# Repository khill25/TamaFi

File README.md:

<div align="center">

  <h1> TamaFi </h1>
  <p> TamaFi is an open-source, WiFi-enabled virtual pet </p>

<!-- Badges -->

<h4>
    <a href="https://twitter.com/techcifer">TWITTER</a>
  <span> · </span>
    <a href="https://www.instagram.com/cifertech/">INSTAGRAM</a>
  <span> · </span>
    <a href="https://www.youtube.com/@techcifer">YOUTUBE</a>
  <span> · </span>
    <a href="https://cifertech.net/">WEBSITE</a>
  </h4>
</div>

<br />

<div>&nbsp;</div>

## 📖 Explore the Full Documentation

Ready to dive deeper into TamaFi's details? Discover the full story, in-depth tutorials, and all the exciting features in our comprehensive [documentation](https://cifertech.net/tamafi-reviving-the-classic-virtual-pet-with-a-tech-twist/). Click the link and explore further!
  
<div>&nbsp;</div>

<!-- About the Project -->
## :star2: About the Project
TamaFi is a modern reimagining of the classic Tamagotchi, aiming to blend nostalgia with modern technology. Built with an ESP32 microcontroller and a vibrant TFT LCD, TamaFi offers a unique twist: feeding your virtual pet through Wi-Fi scanning.

Why TamaFi?
- Classic Tamagotchis lacked vibrant graphics, backlighting, and modern interactions.
- TamaFi fills this gap by offering an enhanced virtual pet experience with open-source versatility.

<div align="center"> 
  
</div>

<div>&nbsp;</div>

<h2>🛠 Functionality Status and Reliability</h2>

TamaFi is a work-in-progress and has room for improvement. While it’s functional and exciting to use, there’s always room to make it better, more reliable, and feature-rich. Whether it’s optimizing the code, enhancing the design, or suggesting new features, your contributions are highly welcomed!

<table>
  <thead>
    <tr>
      <th>Feature</th>
      <th>Status</th>
      <th>Details</th>
    </tr>
  </thead>
  <tbody>
    <tr>
      <td>Pet Animation</td>
      <td>⚠ Stable</td>
      <td>Includes hatching, random, and stat-based animations.</td>
    </tr>
    <tr>
      <td>Stat Management</td>
      <td>⚠ Stable</td>
      <td>Hunger, happiness, and hygiene stats are tracked and updated.</td>
    </tr>
    <tr>
      <td>Wi-Fi Feeding</td>
      <td>🚧 In Progress</td>
      <td>Detects nearby networks and feeds the pet.</td>
    </tr>
    <tr>
      <td>TFT LCD Display</td>
      <td>✅ Reliable</td>
      <td>Displays sprites, stats, and animations with smooth transitions.</td>
    </tr>
    <tr>
      <td>Button Inputs</td>
      <td>⚠ Stable</td>
      <td>Three microswitches handle user interaction.</td>
    </tr>
    <tr>
      <td>PCB Design</td>
      <td>✅ Verified</td>
      <td>Tested for compatibility and efficient layout.</td>
    </tr>
    <tr>
      <td>RGB LED and Buzzer Integration</td>
      <td>🚧 In Progress</td>
      <td>Planned for the next release.</td>
    </tr>
  </tbody>
</table>

<div>&nbsp;</div>

<!-- Features -->
### 🎯 Features

**Hardware:**

- ESP32-U4 microcontroller
- TFT LCD (ST7789) with vibrant visuals
- WS2812 RGB LED for colorful effects
- Buzzer for sound alerts
- TP4056 charging module with USB-C
- LF33 voltage regulator

**Software:**

- Custom animations for pets and stats
- WiFi-based feeding system
- Interactive buttons for actions
- Egg-hatching and pet-death animations
- Open-source and easily customizable

<div>&nbsp;</div>

<!-- License -->
## :warning: License

Distributed under the MIT License. See LICENSE.txt for more information.

<div>&nbsp;</div>

<!-- Contact -->
## :handshake: Contact

▶ Support me on Patreon [patreon.com/cifertech](https://www.patreon.com/cifertech)

CiferTech - [@twitter](https://twitter.com/techcifer) - CiferTech@gmali.com

Project Link: [https://github.com/cifertech/TamaFi](https://github.com/cifertech/TamaFi)

<div>&nbsp;</div>

<!-- Acknowledgments -->
## :gem: Acknowledgements 

**The libraries and projects listed below are used in this software:**
 - [Mecha-Stone Golem](https://darkpixel-kronovi.itch.io/mecha-golem-free)
 - [Fantasy Wooden GUI](https://kanekizlf.itch.io/fantasy-wooden-gui-free)
 - [MyPixelWorld](https://scarloxy.itch.io/mpwsp01)
 - [Transparent Sprites](https://github.com/VolosR/SpritesTuT)

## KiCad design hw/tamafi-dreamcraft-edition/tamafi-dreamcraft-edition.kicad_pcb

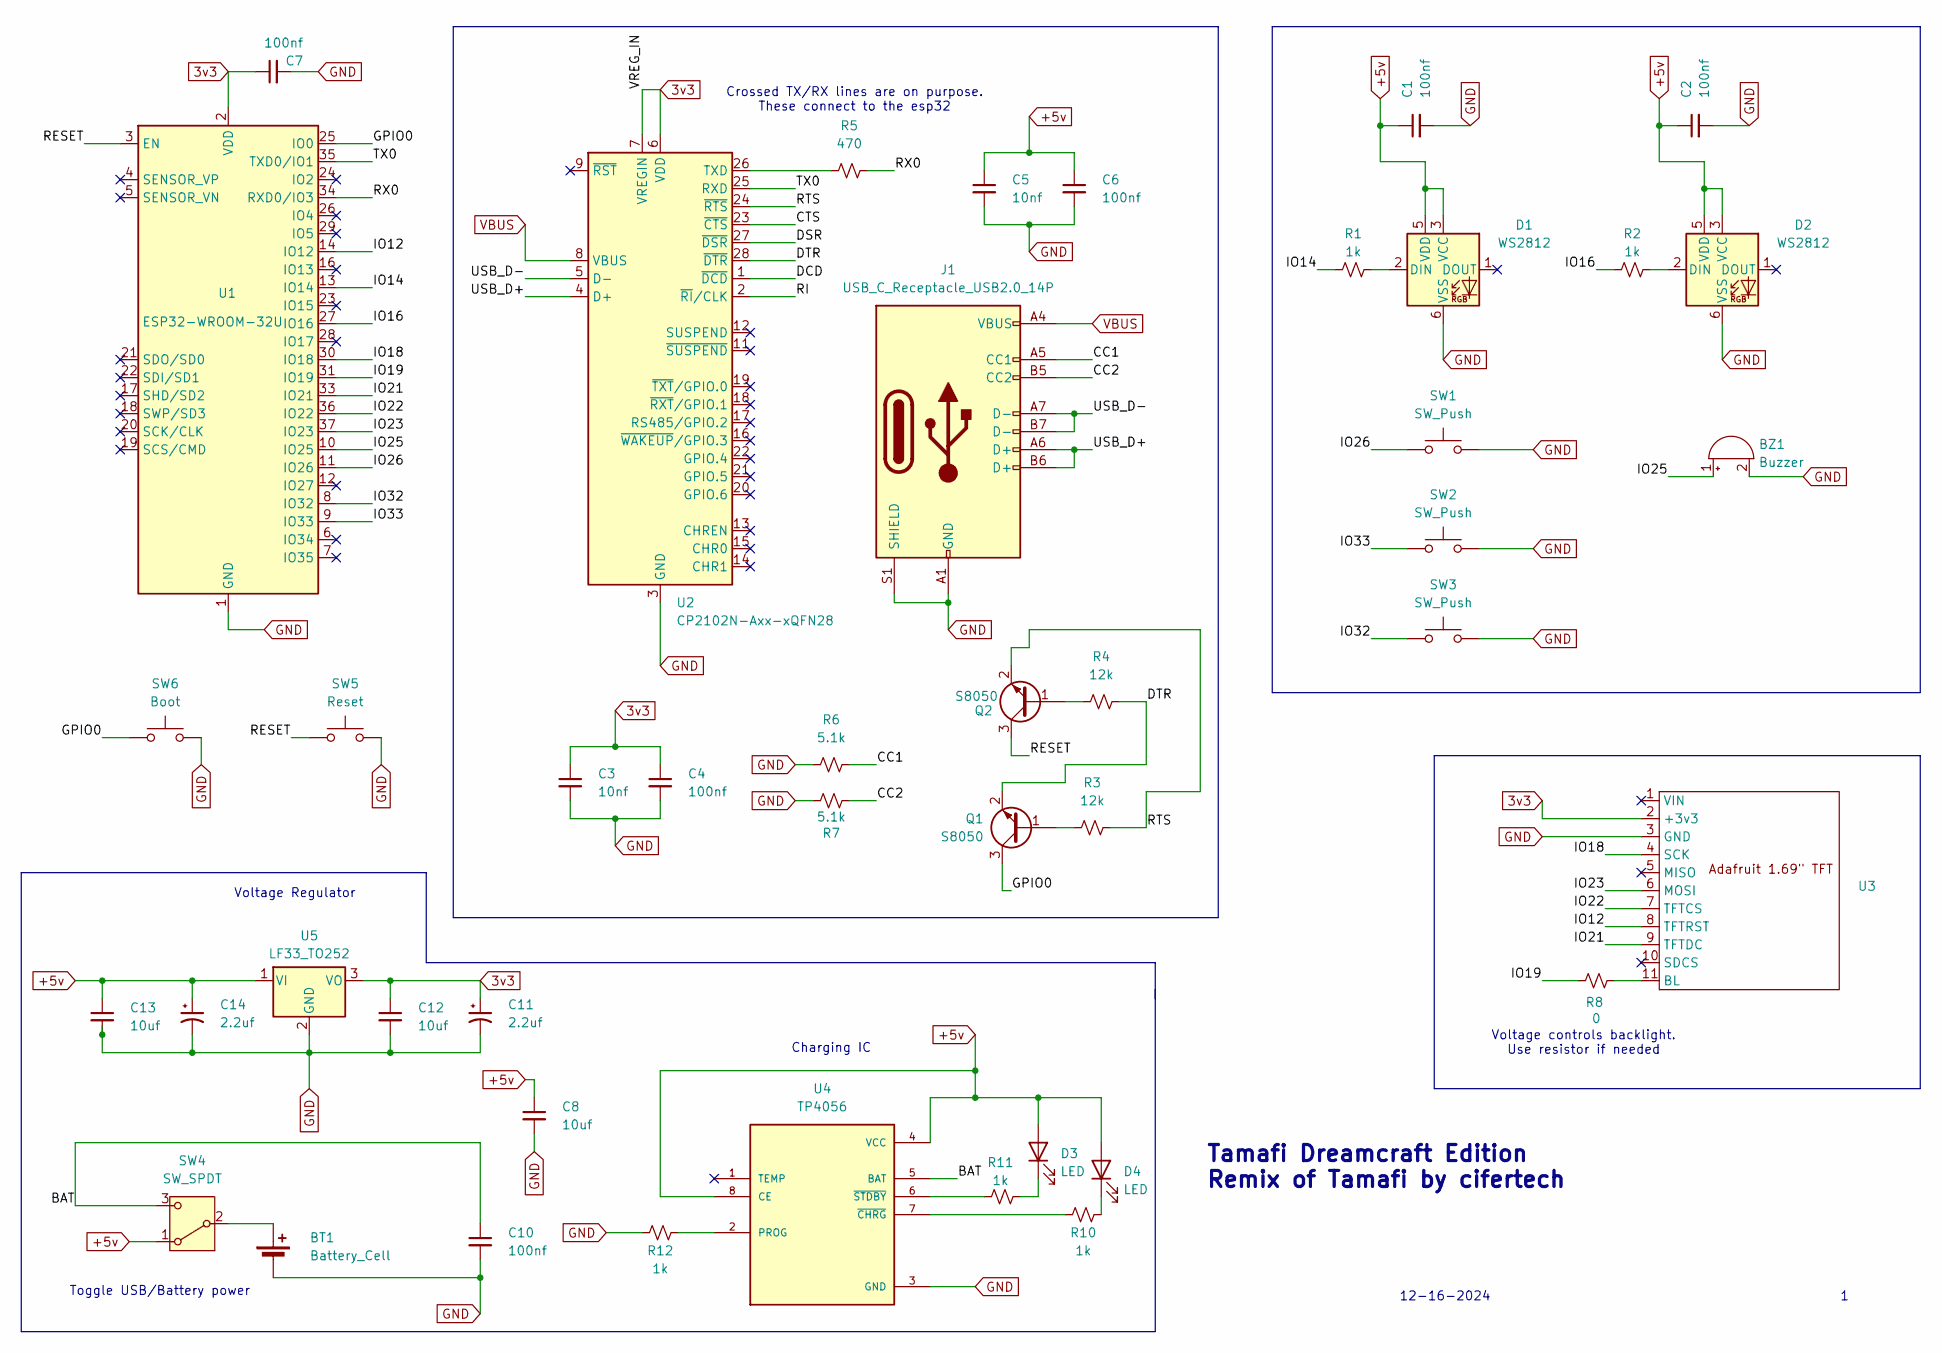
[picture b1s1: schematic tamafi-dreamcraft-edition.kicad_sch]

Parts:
BT1: Battery_Cell; JST_PH_B2B-PH-K_1x02_P2.00mm_Vertical
BZ1: Buzzer; Buzzer_12x9.5RM7.6
C1, C2, C4, C6, C7, C10: 100nf; C_0805_2012Metric
C3, C5: 10nf; C_0805_2012Metric
C8, C12, C13: 10uf; C_0805_2012Metric
C11, C14: 2.2uf; C_0805_2012Metric
D1, D2: WS2812; LED_WS2812_PLCC6_5.0x5.0mm_P1.6mm
D3, D4: LED; LED_0805_2012Metric_Pad1.15x1.40mm_HandSolder
J1: USB_C_Receptacle_USB2.0_14P; USB_C_Receptacle_HRO_TYPE-C-31-M-12
Q1, Q2: S8050; SOT-23
R1, R2, R10, R11, R12: 1k; R_0805_2012Metric
R3, R4: 12k; R_0805_2012Metric
R5: 470; R_0805_2012Metric
R6, R7: 5.1k; R_0805_2012Metric
R8: 0; R_0805_2012Metric
SW1, SW2, SW3: SW_Push; SW_SPST_B3S-1000
SW4: SW_SPDT; SW_Slide-03_Wuerth-WS-SLTV_10x2.5x6.4_P2.54mm
SW5: Reset; SW_SPST_FSMSM
SW6: Boot; SW_SPST_FSMSM
U1: ESP32-WROOM-32U
U2: CP2102N-Axx-xQFN28; QFN-28-1EP_5x5mm_P0.5mm_EP3.35x3.35mm
U3: Adafruit 1.69in 280x240 TFT
U4: TP4056; SOP-8_3.9x4.9mm_P1.27mm
U5: LF33_TO252; TO-252-2

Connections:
3v3: C3.1, C4.1, C7.1, C11.1, C12.1, U1.2 (VDD), U2.6 (VDD), U2.7 (VREGIN), U3.2 (+3v3), U5.3 (VO)
+5v: C1.1, C2.1, C5.1, C6.1, C8.1, C13.1, C14.1, D1.3 (VCC), D1.5 (VDD), D2.3 (VCC), D2.5 (VDD), D3.2 (A), D4.2 (A), SW4.1 (A), U4.4 (VCC), U4.8 (CE), U5.1 (VI)
/BAT: C10.1, SW4.3 (C), U4.5 (BAT)
/CC1: J1.A5 (CC1), R6.2
/CC2: J1.B5 (CC2), R7.2
/CTS: U2.23 (~CTS)
/DCD: U2.1 (~DCD)
/DSR: U2.27 (~DSR)
/DTR: Q1.2 (E), R4.2, U2.28 (~DTR)
/GPIO0: Q1.3 (C), SW6.1, U1.25 (IO0)
/IO12: U1.14 (IO12), U3.8 (TFTRST)
/IO14: R1.2, U1.13 (IO14)
/IO16: R2.2, U1.27 (IO16)
/IO18: U1.30 (IO18), U3.4 (SCK)
/IO19: R8.2, U1.31 (IO19)
/IO21: U1.33 (IO21), U3.9 (TFTDC)
/IO22: U1.36 (IO22), U3.7 (TFTCS)
/IO23: U1.37 (IO23), U3.6 (MOSI)
/IO25: BZ1.1 (+), U1.10 (IO25)
/IO26: SW1.1, U1.11 (IO26)
/IO32: SW3.1, U1.8 (IO32)
/IO33: SW2.1, U1.9 (IO33)
/RESET: Q2.3 (C), SW5.1, U1.3 (EN)
/RI: U2.2 (~RI/CLK)
/RTS: Q2.2 (E), R3.2, U2.24 (~RTS)
/RX0: R5.2, U1.34 (RXD0/IO3)
/TX0: U1.35 (TXD0/IO1), U2.25 (RXD)
/USB_D+: J1.A6 (D+), J1.B6 (D+), U2.4 (D+)
/USB_D-: J1.A7 (D-), J1.B7 (D-), U2.5 (D-)
GND: BT1.2 (-), BZ1.2 (-), C1.2, C2.2, C3.2, C4.2, C5.2, C6.2, C7.2, C8.2, C10.2, C11.2, C12.2, C13.2, C14.2, D1.6 (VSS), D2.6 (VSS), J1.A1 (GND), J1.A12 (GND), J1.B1 (GND), J1.B12 (GND), J1.S1 (SHIELD), R6.1, R7.1, R12.1, SW1.2, SW2.2, SW3.2, SW5.2, SW6.2, U1.1 (GND), U1.15 (GND), U1.38 (GND), U1.39 (GND), U2.3 (GND), U2.29 (GND), U3.3 (GND), U4.3 (GND), U5.2 (GND)
unnamed: BT1.1 (+), SW4.2 (B)
unnamed: D1.2 (DIN), R1.1
unnamed: D2.2 (DIN), R2.1
unnamed: D3.1 (K), R11.1
unnamed: D4.1 (K), R10.2
unnamed: Q1.1 (B), R3.1
unnamed: Q2.1 (B), R4.1
unnamed: R5.1, U2.26 (TXD)
unnamed: R8.1, U3.11 (BL)
unnamed: R12.2, U4.2 (PROG)
unnamed: R10.1, U4.7 (~CHRG)
unnamed: R11.2, U4.6 (~STDBY)
VBUS: J1.A4 (VBUS), J1.A9 (VBUS), J1.B4 (VBUS), J1.B9 (VBUS), U2.8 (VBUS)

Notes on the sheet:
12-16-2024
Charging IC
Voltage Regulator
Toggle USB/Battery power
Crossed TX/RX lines are on purpose. These connect to the esp32
Voltage controls backlight. Use resistor if needed
Tamafi Dreamcraft Edition Remix of Tamafi by cifertech

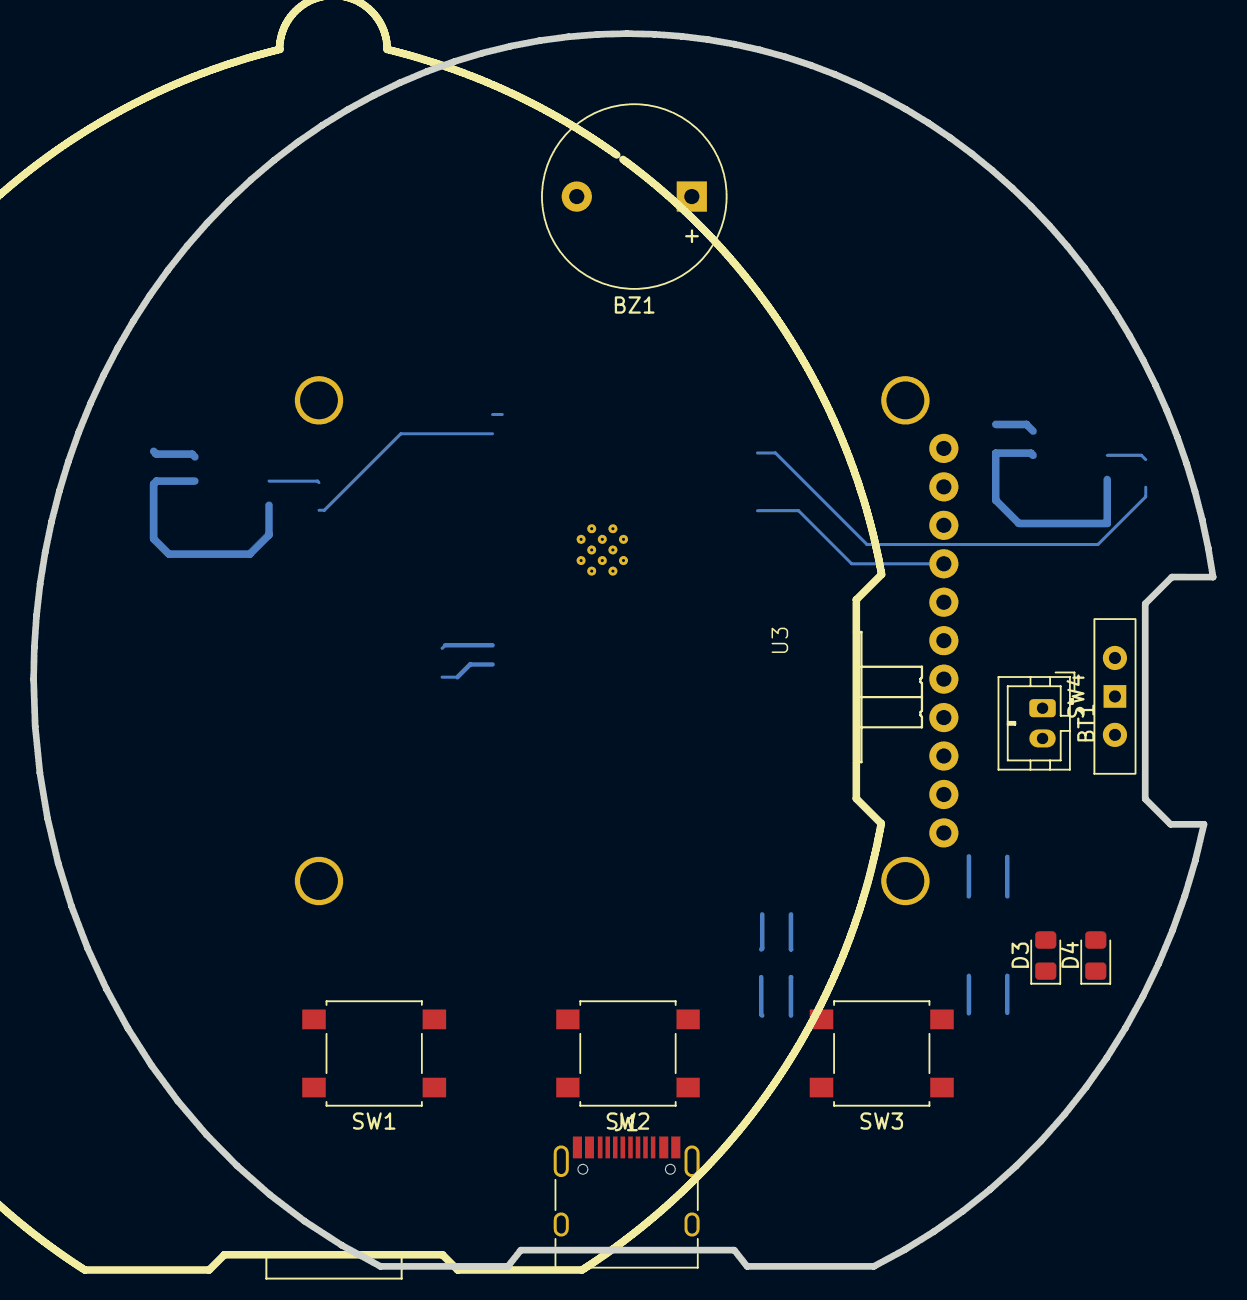
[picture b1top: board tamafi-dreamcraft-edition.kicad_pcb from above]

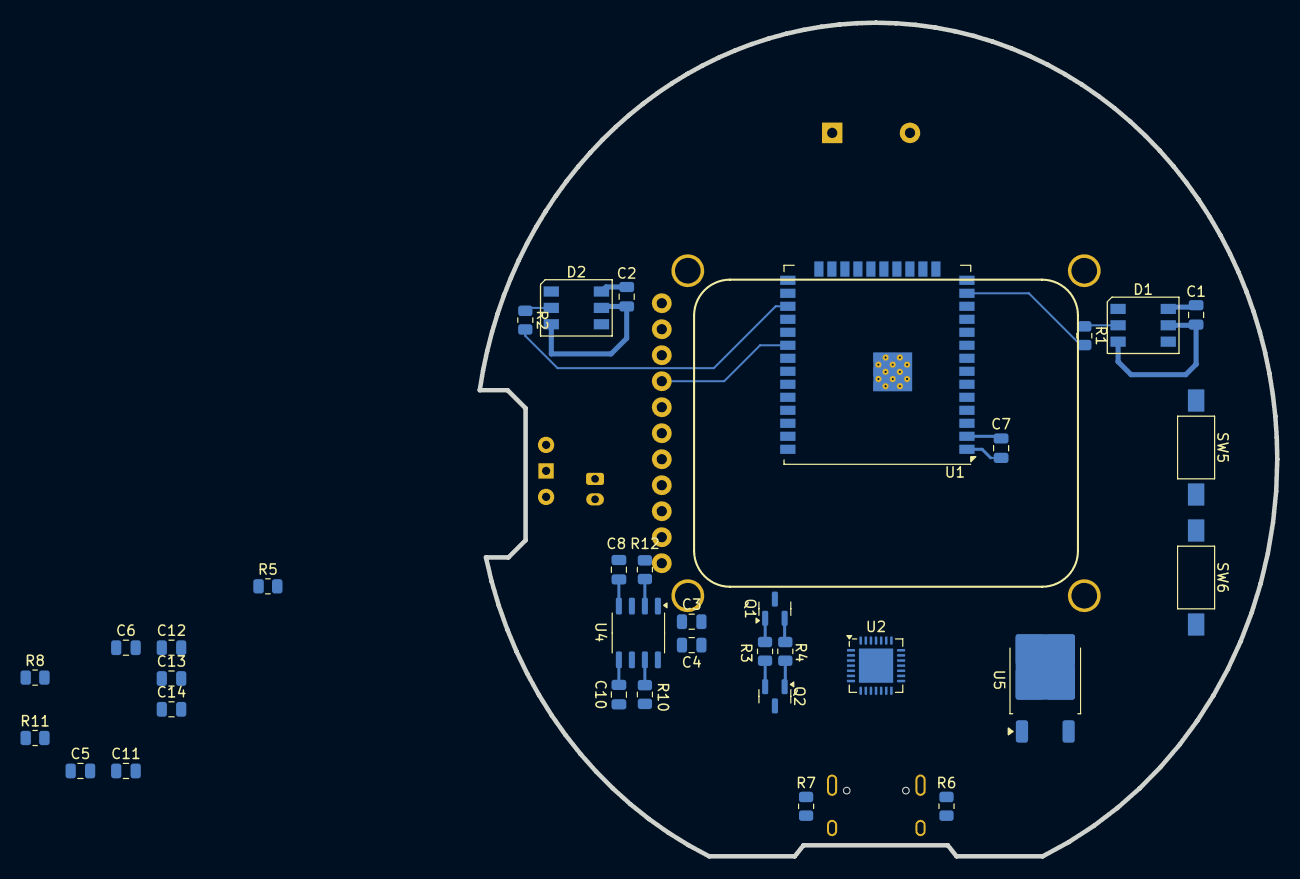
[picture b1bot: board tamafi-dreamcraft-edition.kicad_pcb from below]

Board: 2 copper layers, 77.9 x 81.4 mm, 44 parts (34 on the bottom side), 39 nets.

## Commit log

2024-12-02 Update LICENSE
2024-12-27 My version of the board. Placement almost finished, routing tdb
